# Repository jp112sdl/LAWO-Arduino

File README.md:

# LAWO-FlipDot
Arduino library for LAWO XY5 flipdot displays (also for GORBA and other FP2800 based flipdot displays)

### BOM (mostly from reichelt.de)

| Qty	| Reference(s)	| Value |	Order No. / URL	| Supplier
|------|------------|---------------|-------------|-------------|
|1|	C1	|100u	|RAD 100/25|	reichelt
|3 |	C2, C3, C4|100n|	X7R-5 100N	|reichelt
|1|	F1	|T500mA	|RND 170-00041	|reichelt
|1|	F1	|Fuse Holder |RND 170-00188 |reichelt
|1|P1	|MATRIX	|WSL 50G	|reichelt
|1|P2	|MUX|	WSL 20G	|reichelt
|1|Q1	|BC547|	BC 547C	|reichelt
|1|Q2	|IRF740	|IRF 740	|reichelt
|1|	R4|	56|	2W METALL 56	|reichelt
|1|	RV1|	5k|	64W-5,0K|	reichelt
|1	|U1|LC78_05-0.5	|LC78_05-0.5	|reichelt
|1|	U2	|LM317T	|LM 317-220	|reichelt
|1| J1 | Barrel Jack | DC BU25 90|reichelt
|1| J2 | 1x6 Screw Terminal Block, 5mm | RND 205-00049 |reichelt
|1| D1| 1N4001 | 1N 4001|reichelt|
|1| D2| LED1 | LED 3MM GN |reichelt|
|1| D3| LED2 | LED 3MM RT|reichelt
|2| SW1, SW2| TASTER 9303 | reichelt
|4| U4,U5,U6,U7	|Sockel	|GS 18	|reichelt
|2|U8,U9	|Sockel	|GS 28-S	|reichelt
|2| U5,U4	|ULN2803A	|ULN 2803A|	reichelt
|2	|U6,U7	|UDN2981A	|UDN 2981	|reichelt
|2| U8, U9 | MCP23017 | MCP 23017-E/SP | reichelt
|2| R13, R14 | 330 SMD 0805 | RND 0805 1 330 | reichelt
|1| R3 | 240 SMD 0805 | RND 0805 1 240 | reichelt
|2| R17, R18 | 4k7 SMD 0805 | RND 0805 1 4,7K  | reichelt
|12| R1, R2, R5, R6, R7, R8, R9, R10, R11, R12, R15, R16 | 10k SMD 0805 | RND 0805 1 10K  | reichelt
| 1 | U3 | ESP32 Module | AZDelivery ESP32 NodeMCU Module | [amazon.de](https://www.amazon.de/AZDelivery-NodeMCU-Development-Nachfolgermodell-ESP8266/dp/B071P98VTG/ref=sxts_sxwds-bia-wc-p13n1_0)

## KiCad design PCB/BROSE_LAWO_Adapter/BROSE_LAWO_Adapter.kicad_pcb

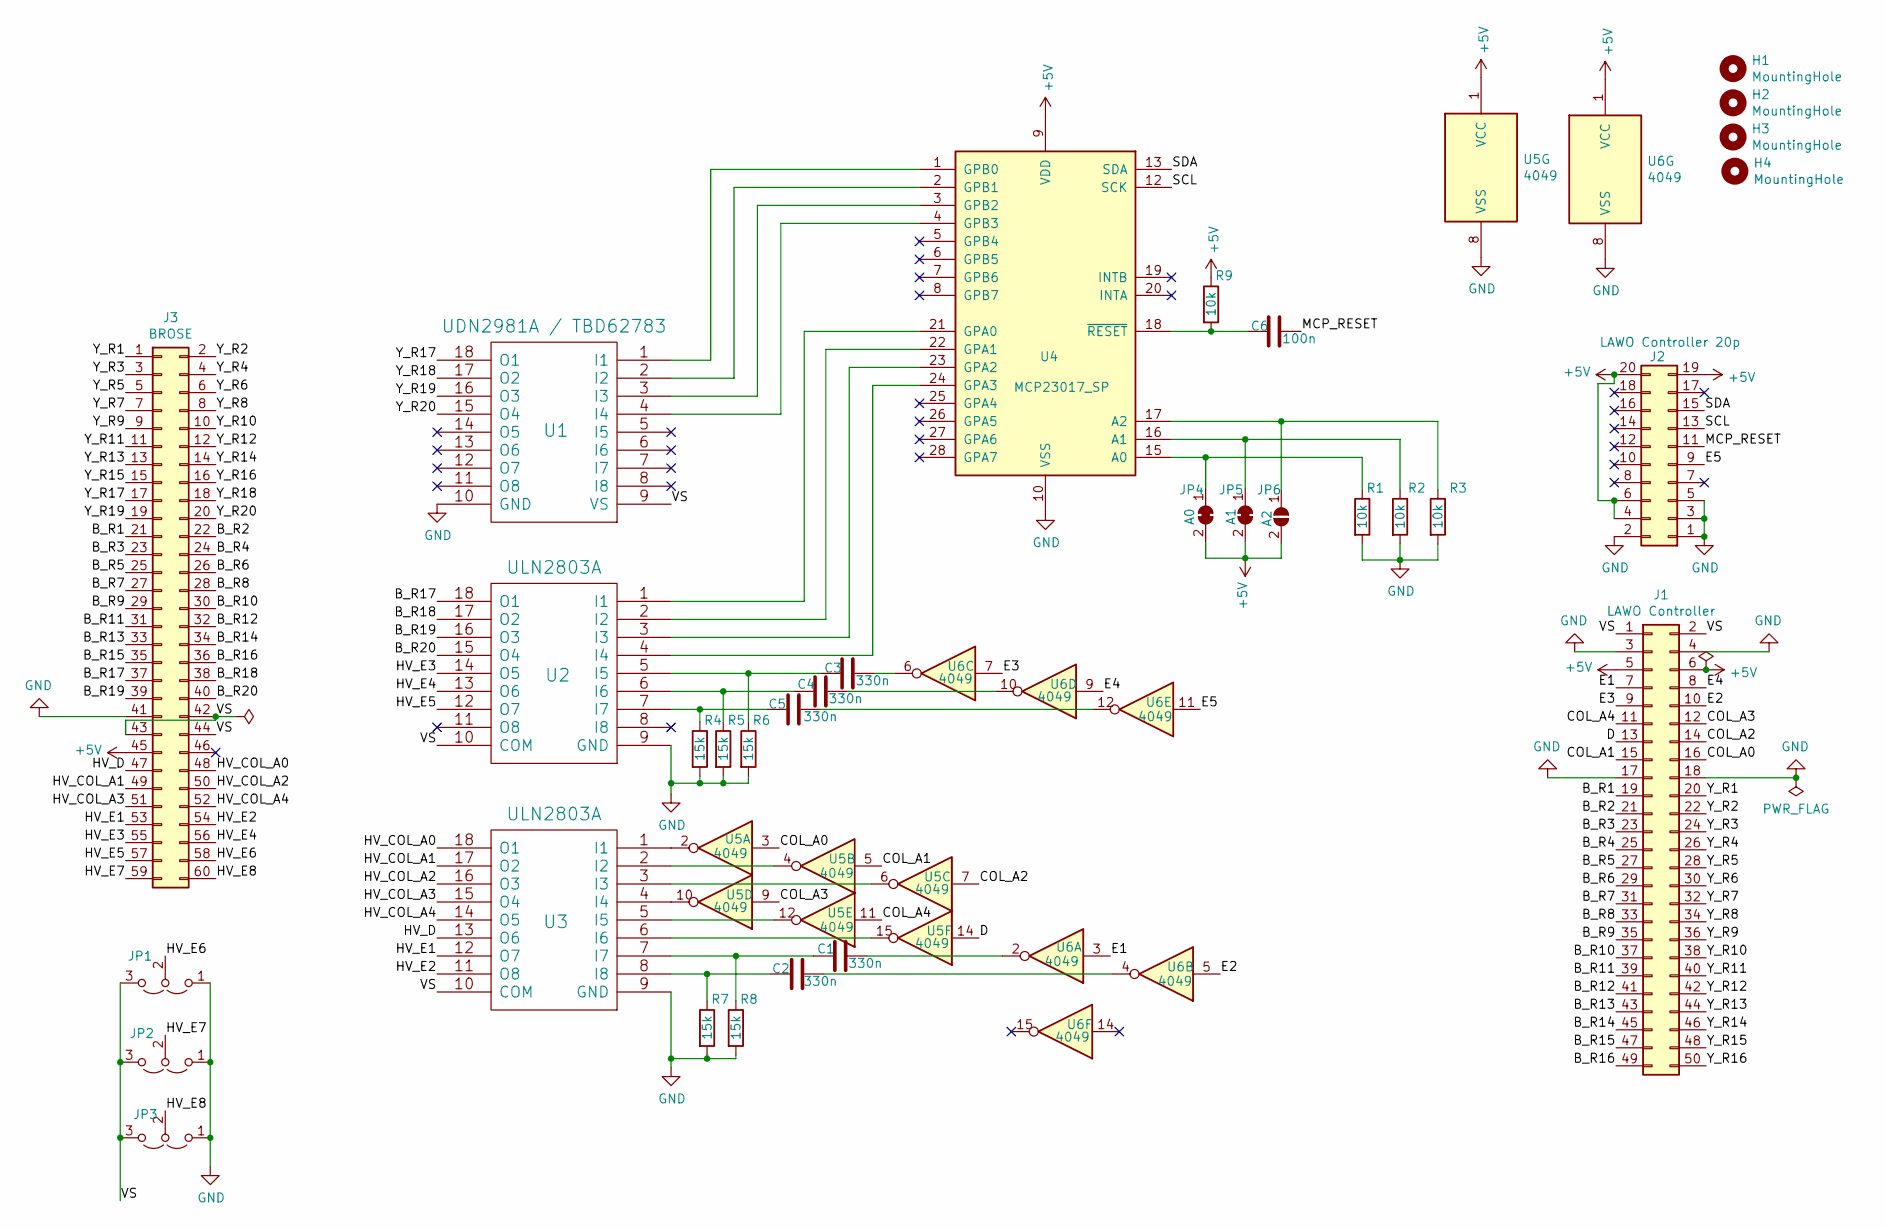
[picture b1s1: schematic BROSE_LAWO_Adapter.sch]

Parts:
C1, C2, C3, C4, C5: 330n; C_Rect_L10.0mm_W4.0mm_P7.50mm_MKS4
C6: 100n; C_0805_2012Metric_Pad1.15x1.40mm_HandSolder
H1, H2, H3, H4: MountingHole; 1pin
J1: LAWO Controller; IDC-Header_2x25_P2.54mm_Vertical
J2: LAWO Controller 20p; IDC-Header_2x10_P2.54mm_Vertical
J3: BROSE; IDC-Header_2x30_P2.54mm_Vertical
JP1: E6; PinHeader_1x03_P2.54mm_Vertical
JP2: E7; PinHeader_1x03_P2.54mm_Vertical
JP3: E8; PinHeader_1x03_P2.54mm_Vertical
JP4: A0; SolderJumper-2_P1.3mm_Bridged_RoundedPad1.0x1.5mm
JP5: A1; SolderJumper-2_P1.3mm_Bridged_RoundedPad1.0x1.5mm
JP6: A2; SolderJumper-2_P1.3mm_Open_RoundedPad1.0x1.5mm
R1, R2, R3, R9: 10k; R_0805_2012Metric_Pad1.15x1.40mm_HandSolder
R4, R5, R6, R7, R8: 15k; R_Axial_DIN0204_L3.6mm_D1.6mm_P2.54mm_Vertical
U1: UDN2981A / TBD62783; DIP-18_W7.62mm_Socket
U2, U3: ULN2803A; DIP-18_W7.62mm_Socket
U4: MCP23017_SP; DIP-28_W7.62mm_Socket
U5, U6: 4049; DIP-16_W7.62mm_Socket

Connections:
+5V: J1.5, J1.6, J2.4, J2.6, J2.19, J2.20, J3.45, JP4.2 (B), JP5.2 (B), JP6.2 (B), R9.1, U4.9 (VDD), U5.1 (VCC), U6.1 (VCC)
/B_R1: J1.19, J3.21
/B_R2: J1.21, J3.22
/B_R3: J1.23, J3.23
/B_R4: J1.25, J3.24
/B_R5: J1.27, J3.25
/B_R6: J1.29, J3.26
/B_R7: J1.31, J3.27
/B_R8: J1.33, J3.28
/B_R9: J1.35, J3.29
/B_R10: J1.37, J3.30
/B_R11: J1.39, J3.31
/B_R12: J1.41, J3.32
/B_R13: J1.43, J3.33
/B_R14: J1.45, J3.34
/B_R15: J1.47, J3.35
/B_R16: J1.49, J3.36
/B_R17: J3.37, U2.18 (O1)
/B_R18: J3.38, U2.17 (O2)
/B_R19: J3.39, U2.16 (O3)
/B_R20: J3.40, U2.15 (O4)
/COL_A0: J1.16, U5.3
/COL_A1: J1.15, U5.5
/COL_A2: J1.14, U5.7
/COL_A3: J1.12, U5.9
/COL_A4: J1.11, U5.11
/D: J1.13, U5.14
/E1: J1.7, U6.3
/E2: J1.10, U6.5
/E3: J1.9, U6.7
/E4: J1.8, U6.9
/E5: J2.9, U6.11
/HV_COL_A0: J3.48, U3.18 (O1)
/HV_COL_A1: J3.49, U3.17 (O2)
/HV_COL_A2: J3.50, U3.16 (O3)
/HV_COL_A3: J3.51, U3.15 (O4)
/HV_COL_A4: J3.52, U3.14 (O5)
/HV_D: J3.47, U3.13 (O6)
/HV_E1: J3.53, U3.12 (O7)
/HV_E2: J3.54, U3.11 (O8)
/HV_E3: J3.55, U2.14 (O5)
/HV_E4: J3.56, U2.13 (O6)
/HV_E5: J3.57, U2.12 (O7)
/HV_E6: J3.58, JP1.2 (C)
/HV_E7: J3.59, JP2.2 (C)
/HV_E8: J3.60, JP3.2 (C)
/MCP_RESET: C6.2, J2.11
/SCL: J2.13, U4.12 (SCK)
/SDA: J2.15, U4.13 (SDA)
/VS: J1.1, J1.2, J3.42, J3.43, J3.44, JP1.3 (B), JP2.3 (B), JP3.3 (B), U1.9 (VS), U2.10 (COM), U3.10 (COM)
/Y_R1: J1.20, J3.1
/Y_R2: J1.22, J3.2
/Y_R3: J1.24, J3.3
/Y_R4: J1.26, J3.4
/Y_R5: J1.28, J3.5
/Y_R6: J1.30, J3.6
/Y_R7: J1.32, J3.7
/Y_R8: J1.34, J3.8
/Y_R9: J1.36, J3.9
/Y_R10: J1.38, J3.10
/Y_R11: J1.40, J3.11
/Y_R12: J1.42, J3.12
/Y_R13: J1.44, J3.13
/Y_R14: J1.46, J3.14
/Y_R15: J1.48, J3.15
/Y_R16: J1.50, J3.16
/Y_R17: J3.17, U1.18 (O1)
/Y_R18: J3.18, U1.17 (O2)
/Y_R19: J3.19, U1.16 (O3)
/Y_R20: J3.20, U1.15 (O4)
GND: J1.3, J1.4, J1.17, J1.18, J2.1, J2.2, J2.3, J2.5, J3.41, JP1.1 (A), JP2.1 (A), JP3.1 (A), R1.2, R2.2, R3.2, R4.2, R5.2, R6.2, R7.2, R8.2, U1.10 (GND), U2.9 (GND), U3.9 (GND), U4.10 (VSS), U5.8 (VSS), U6.8 (VSS)
unnamed: C1.1, R8.1, U3.7 (I7)
unnamed: C1.2, U6.2
unnamed: C2.1, R7.1, U3.8 (I8)
unnamed: C2.2, U6.4
unnamed: C3.1, R6.1, U2.5 (I5)
unnamed: C3.2, U6.6
unnamed: C4.1, R5.1, U2.6 (I6)
unnamed: C4.2, U6.10
unnamed: C5.1, R4.1, U2.7 (I7)
unnamed: C5.2, U6.12
unnamed: C6.1, R9.2, U4.18 (~RESET~)
unnamed: JP4.1 (A), R1.1, U4.15 (A0)
unnamed: JP5.1 (A), R2.1, U4.16 (A1)
unnamed: JP6.1 (A), R3.1, U4.17 (A2)
unnamed: U1.1 (I1), U4.1 (GPB0)
unnamed: U1.2 (I2), U4.2 (GPB1)
unnamed: U1.3 (I3), U4.3 (GPB2)
unnamed: U1.4 (I4), U4.4 (GPB3)
unnamed: U2.1 (I1), U4.21 (GPA0)
unnamed: U2.2 (I2), U4.22 (GPA1)
unnamed: U2.3 (I3), U4.23 (GPA2)
unnamed: U2.4 (I4), U4.24 (GPA3)
unnamed: U3.1 (I1), U5.2
unnamed: U3.2 (I2), U5.4
unnamed: U3.3 (I3), U5.6
unnamed: U3.4 (I4), U5.10
unnamed: U3.5 (I5), U5.12
unnamed: U3.6 (I6), U5.15

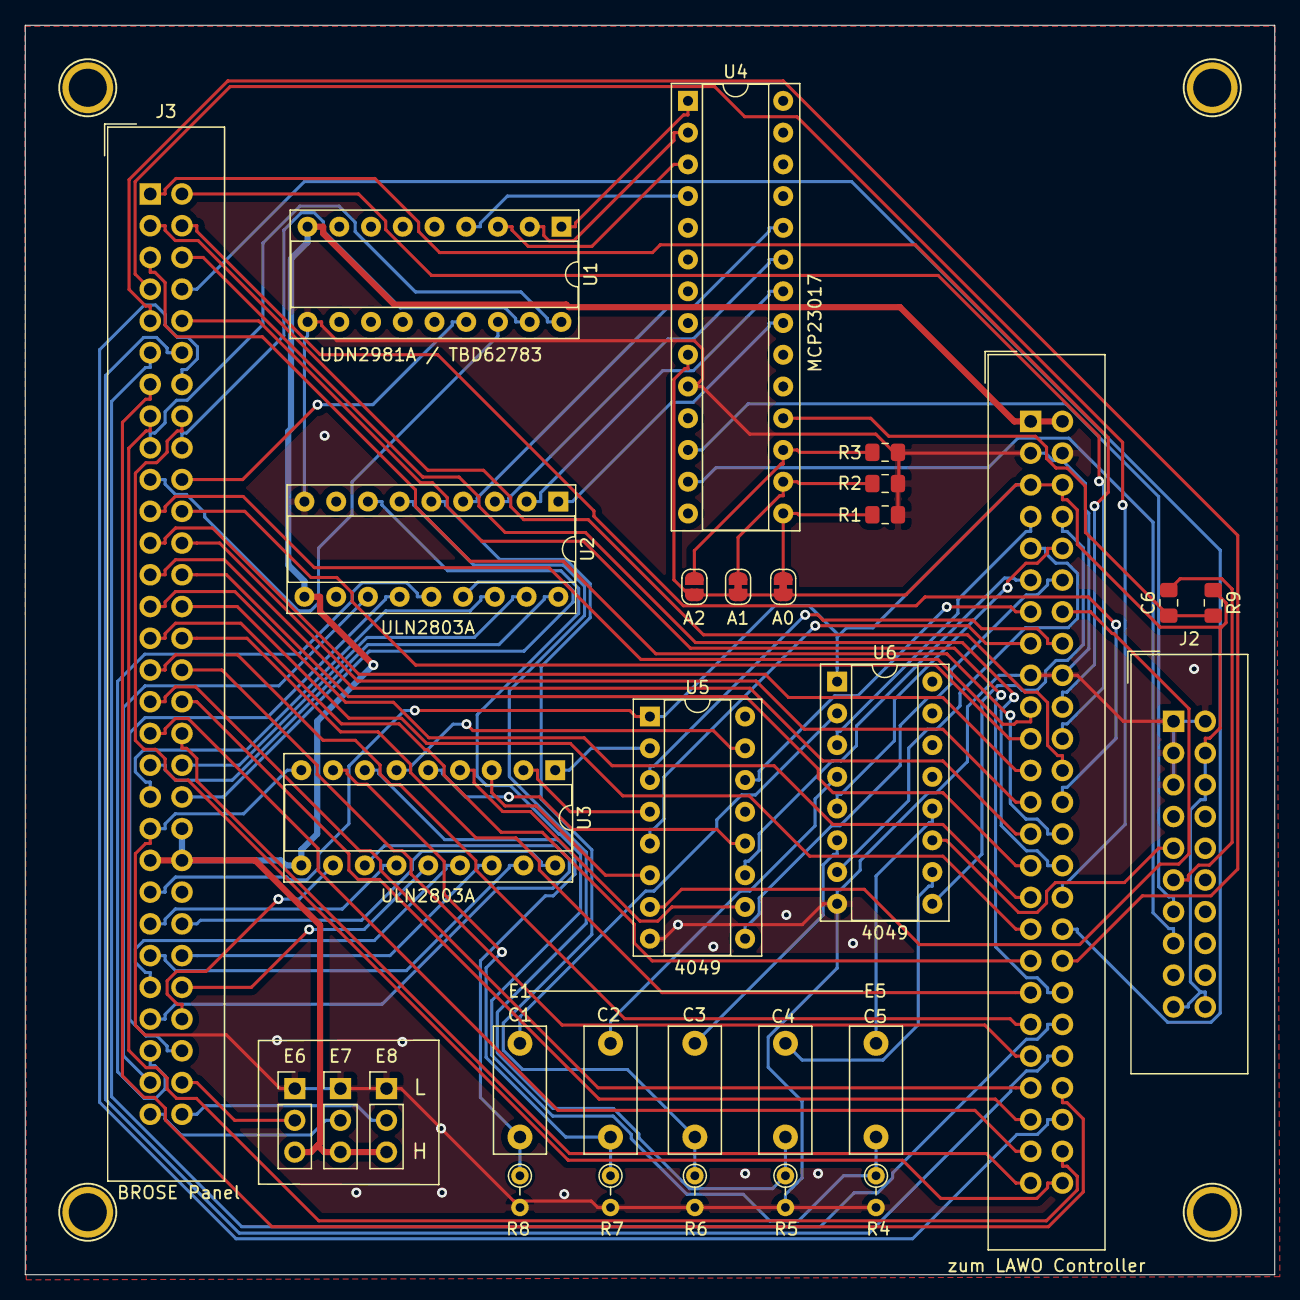
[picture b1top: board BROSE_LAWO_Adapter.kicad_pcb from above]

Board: 2 copper layers, 100.0 x 100.0 mm, 34 parts (0 on the bottom side), 99 nets.

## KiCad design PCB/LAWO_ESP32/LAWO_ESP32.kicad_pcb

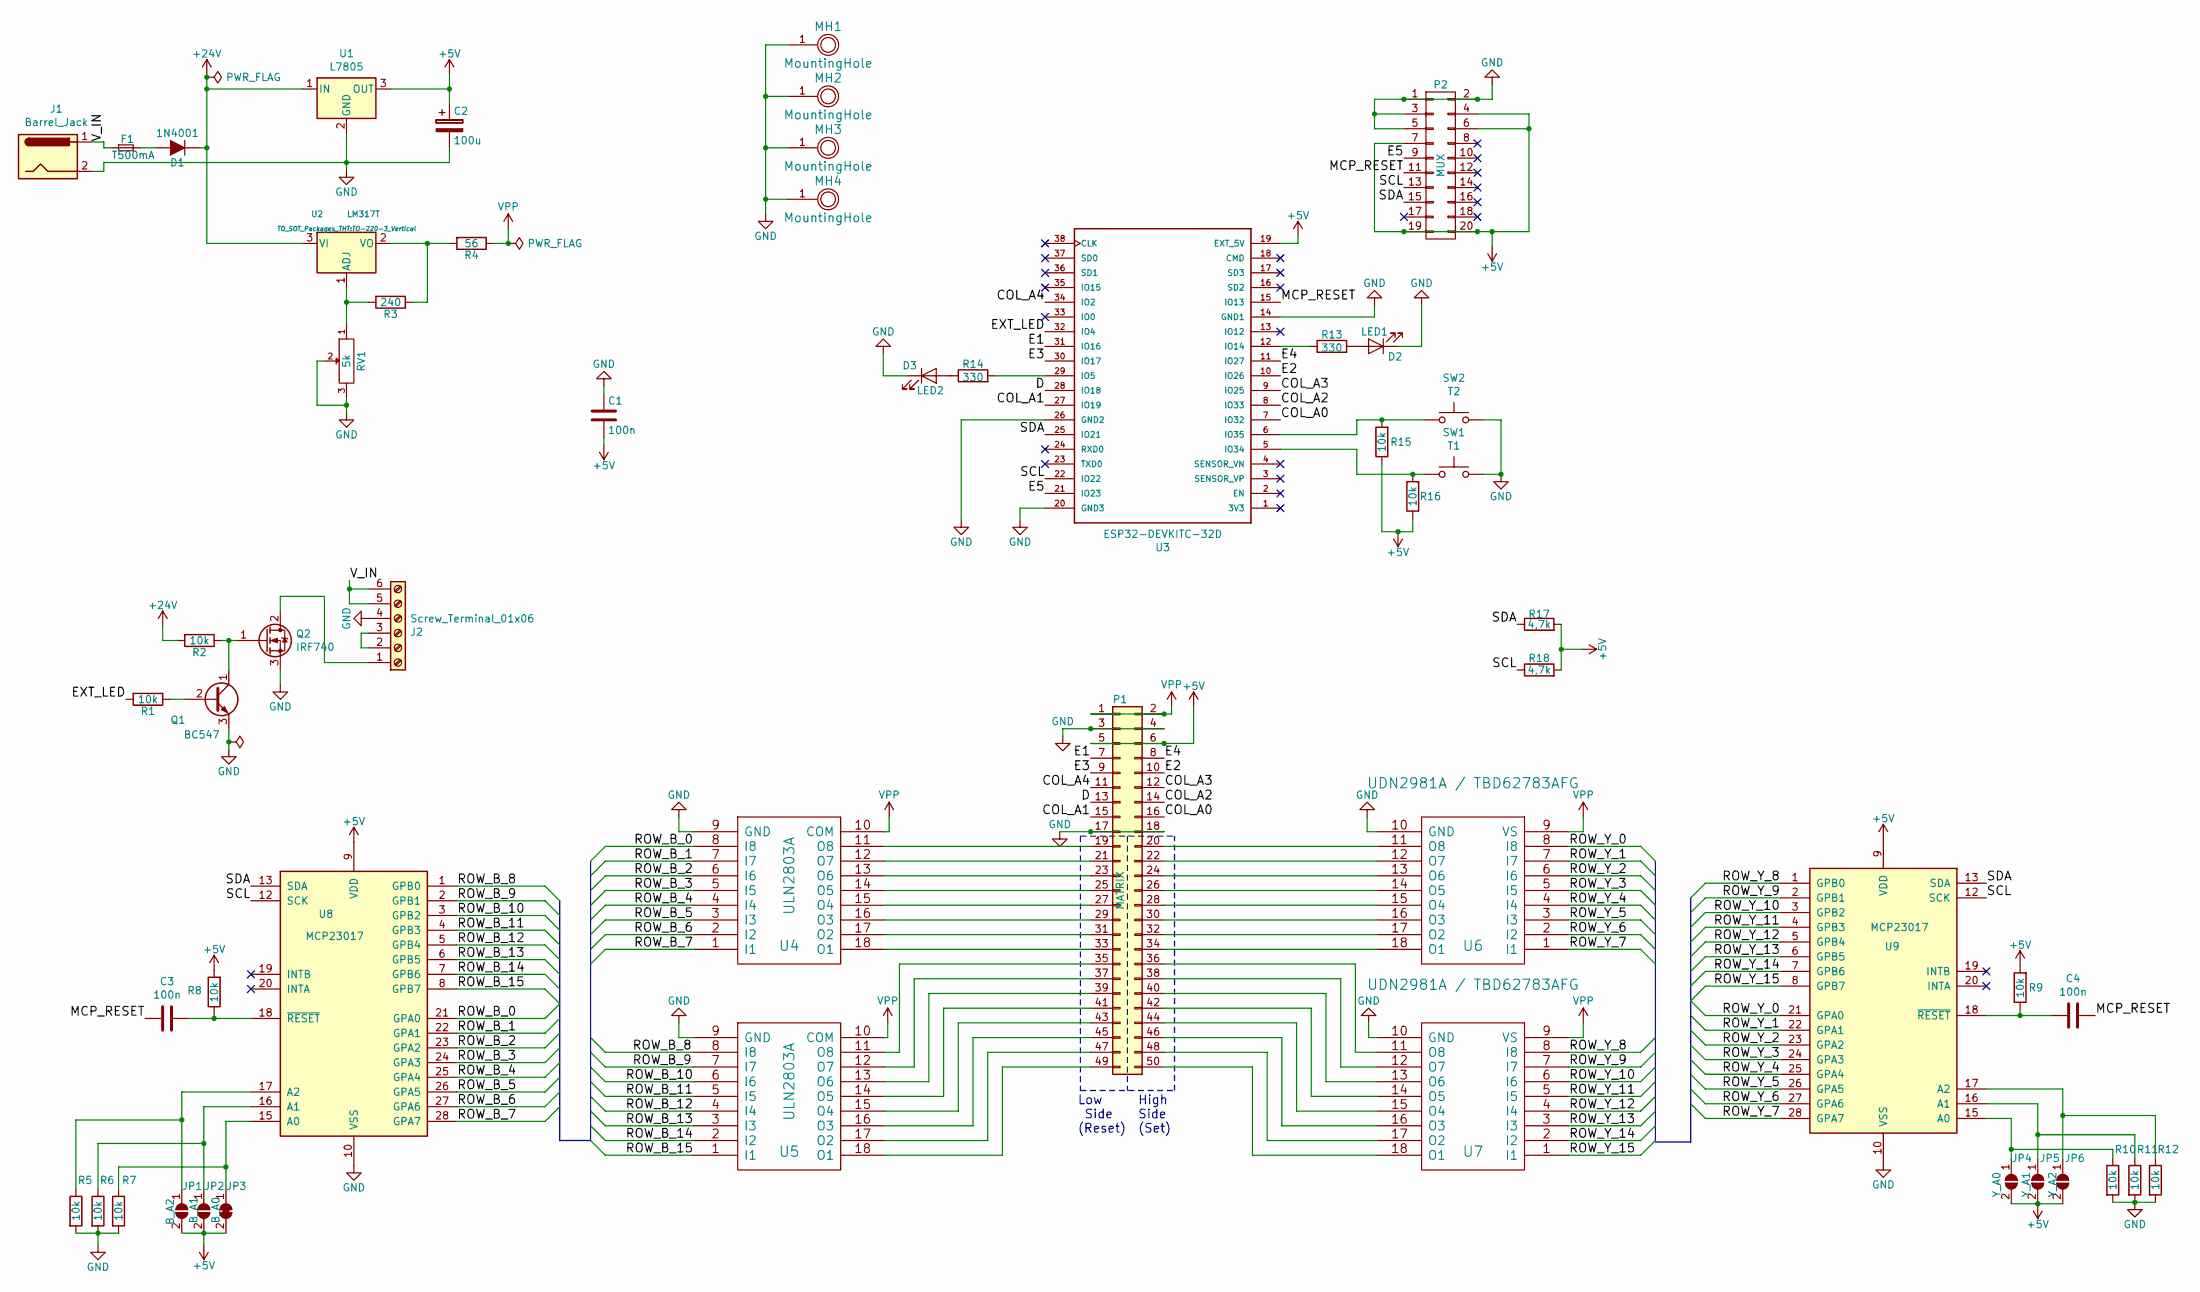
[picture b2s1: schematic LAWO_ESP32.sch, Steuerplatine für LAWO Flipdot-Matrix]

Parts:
C1, C3, C4: 100n; C_0805_2012Metric_Pad1.15x1.40mm_HandSolder
C2: 100u; CP_Radial_D5.0mm_P2.00mm
D1: 1N4001; D_DO-41_SOD81_P10.16mm_Horizontal
D2: LED1; LED_D3.0mm
D3: LED2; LED_D3.0mm
F1: T500mA; Fuseholder5x20_horiz_open_Schurter_0031_8201
J1: Barrel_Jack; BARREL_JACK
J2: Screw_Terminal_01x06; TerminalBlock_bornier-6_P5.08mm
JP1: B_A2; SolderJumper-2_P1.3mm_Open_RoundedPad1.0x1.5mm
JP2: B_A1; SolderJumper-2_P1.3mm_Open_RoundedPad1.0x1.5mm
JP3: B_A0; SolderJumper-2_P1.3mm_Bridged2Bar_RoundedPad1.0x1.5mm
JP4: Y_A0; SolderJumper-2_P1.3mm_Open_RoundedPad1.0x1.5mm
JP5: Y_A1; SolderJumper-2_P1.3mm_Open_RoundedPad1.0x1.5mm
JP6: Y_A2; SolderJumper-2_P1.3mm_Open_RoundedPad1.0x1.5mm
MH1, MH2, MH3, MH4: MountingHole; 1pin
P1: MATRIX; IDC_Header_Straight_50pins
P2: MUX; IDC_Header_Straight_20pins
Q1: BC547; TO-92_HandSolder
Q2: IRF740; TO-220-3_Vertical
R1, R2, R5, R6, R7, R8, R9, R10, R11, R12, R15, R16: 10k; R_0805_2012Metric
R3: 240; R_0805_2012Metric
R4: 56; R_Axial_DIN0411_L9.9mm_D3.6mm_P15.24mm_Horizontal
R13, R14: 330; R_0805_2012Metric
R17, R18: 4,7k; R_0805_2012Metric
RV1: 5k; Potentiometer_Trimmer_Bourns_3299W
SW1: T1; SW_PUSH_6mm_h5mm
SW2: T2; SW_PUSH_6mm_h5mm
U1: L7805; SIP3_11.6x8.5mm
U2: LM317T; TO-220-3_Vertical
U3: ESP32-DEVKITC-32D; MODULE_ESP32-DEVKITC-32D
U4, U5: ULN2803A; DIP-18_W7.62mm_Socket
U6, U7: UDN2981A / TBD62783AFG; DIP-18_W7.62mm_Socket
U8, U9: MCP23017; DIP-28_W7.62mm_Socket

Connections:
+5V: C1.2, C2.1, JP1.2 (B), JP2.2 (B), JP3.2 (B), JP4.2 (B), JP5.2 (B), JP6.2 (B), P1.5, P1.6, P2.4, P2.6, P2.7, P2.19, P2.20, R8.2, R9.2, R15.1, R16.1, R17.2, R18.2, U1.3 (OUT), U3.19 (EXT_5V), U8.9 (VDD), U9.9 (VDD)
+24V: D1.1 (K), R2.2, U1.1 (IN), U2.3 (VI)
/COL_A0: P1.16, U3.7 (IO32)
/COL_A1: P1.15, U3.27 (IO19)
/COL_A2: P1.14, U3.8 (IO33)
/COL_A3: P1.12, U3.9 (IO25)
/COL_A4: P1.11, U3.34 (IO2)
/D: P1.13, U3.28 (IO18)
/E1: P1.7, U3.31 (IO16)
/E2: P1.10, U3.10 (IO26)
/E3: P1.9, U3.30 (IO17)
/E4: P1.8, U3.11 (IO27)
/E5: P2.9, U3.21 (IO23)
/EXT_LED: R1.2, U3.32 (IO4)
/MCP_RESET: C3.2, C4.1, P2.11, U3.15 (IO13)
/ROW_B_0: U4.8 (I8), U8.21 (GPA0)
/ROW_B_1: U4.7 (I7), U8.22 (GPA1)
/ROW_B_2: U4.6 (I6), U8.23 (GPA2)
/ROW_B_3: U4.5 (I5), U8.24 (GPA3)
/ROW_B_4: U4.4 (I4), U8.25 (GPA4)
/ROW_B_5: U4.3 (I3), U8.26 (GPA5)
/ROW_B_6: U4.2 (I2), U8.27 (GPA6)
/ROW_B_7: U4.1 (I1), U8.28 (GPA7)
/ROW_B_8: U5.8 (I8), U8.1 (GPB0)
/ROW_B_9: U5.7 (I7), U8.2 (GPB1)
/ROW_B_10: U5.6 (I6), U8.3 (GPB2)
/ROW_B_11: U5.5 (I5), U8.4 (GPB3)
/ROW_B_12: U5.4 (I4), U8.5 (GPB4)
/ROW_B_13: U5.3 (I3), U8.6 (GPB5)
/ROW_B_14: U5.2 (I2), U8.7 (GPB6)
/ROW_B_15: U5.1 (I1), U8.8 (GPB7)
/ROW_Y_0: U6.8 (I8), U9.21 (GPA0)
/ROW_Y_1: U6.7 (I7), U9.22 (GPA1)
/ROW_Y_2: U6.6 (I6), U9.23 (GPA2)
/ROW_Y_3: U6.5 (I5), U9.24 (GPA3)
/ROW_Y_4: U6.4 (I4), U9.25 (GPA4)
/ROW_Y_5: U6.3 (I3), U9.26 (GPA5)
/ROW_Y_6: U6.2 (I2), U9.27 (GPA6)
/ROW_Y_7: U6.1 (I1), U9.28 (GPA7)
/ROW_Y_8: U7.8 (I8), U9.1 (GPB0)
/ROW_Y_9: U7.7 (I7), U9.2 (GPB1)
/ROW_Y_10: U7.6 (I6), U9.3 (GPB2)
/ROW_Y_11: U7.5 (I5), U9.4 (GPB3)
/ROW_Y_12: U7.4 (I4), U9.5 (GPB4)
/ROW_Y_13: U7.3 (I3), U9.6 (GPB5)
/ROW_Y_14: U7.2 (I2), U9.7 (GPB6)
/ROW_Y_15: U7.1 (I1), U9.8 (GPB7)
/SCL: P2.13, R18.1, U3.22 (IO22), U8.12 (SCK), U9.12 (SCK)
/SDA: P2.15, R17.1, U3.25 (IO21), U8.13 (SDA), U9.13 (SDA)
/V_IN: F1.1, J1.1, J2.5, J2.6
GND: C1.1, C2.2, D2.1 (K), D3.1 (K), J1.2, J2.4, MH1.1, MH2.1, MH3.1, MH4.1, P1.3, P1.4, P1.17, P1.18, P2.1, P2.2, P2.3, P2.5, Q1.3 (E), Q2.3 (S), R5.2, R6.2, R7.2, R10.2, R11.2, R12.2, RV1.2, RV1.3, SW1.2, SW2.2, U1.2 (GND), U3.14 (GND1), U3.20 (GND3), U3.26 (GND2), U4.9 (GND), U5.9 (GND), U6.10 (GND), U7.10 (GND), U8.10 (VSS), U9.10 (VSS)
unnamed: C3.1, R8.1, U8.18 (~RESET~)
unnamed: C4.2, R9.1, U9.18 (~RESET~)
unnamed: D1.2 (A), F1.2
unnamed: D2.2 (A), R13.2
unnamed: D3.2 (A), R14.1
unnamed: J2.1, Q2.2 (D)
unnamed: J2.2, J2.3
unnamed: JP1.1 (A), R5.1, U8.17 (A2)
unnamed: JP2.1 (A), R6.1, U8.16 (A1)
unnamed: JP3.1 (A), R7.1, U8.15 (A0)
unnamed: JP4.1 (A), R10.1, U9.15 (A0)
unnamed: JP5.1 (A), R11.1, U9.16 (A1)
unnamed: JP6.1 (A), R12.1, U9.17 (A2)
unnamed: P1.19, U4.11 (O8)
unnamed: P1.20, U6.11 (O8)
unnamed: P1.21, U4.12 (O7)
unnamed: P1.22, U6.12 (O7)
unnamed: P1.23, U4.13 (O6)
unnamed: P1.24, U6.13 (O6)
unnamed: P1.25, U4.14 (O5)
unnamed: P1.26, U6.14 (O5)
unnamed: P1.27, U4.15 (O4)
unnamed: P1.28, U6.15 (O4)
unnamed: P1.29, U4.16 (O3)
unnamed: P1.30, U6.16 (O3)
unnamed: P1.31, U4.17 (O2)
unnamed: P1.32, U6.17 (O2)
unnamed: P1.33, U4.18 (O1)
unnamed: P1.34, U6.18 (O1)
unnamed: P1.35, U5.11 (O8)
unnamed: P1.36, U7.11 (O8)
unnamed: P1.37, U5.12 (O7)
unnamed: P1.38, U7.12 (O7)
unnamed: P1.39, U5.13 (O6)
unnamed: P1.40, U7.13 (O6)
unnamed: P1.41, U5.14 (O5)
unnamed: P1.42, U7.14 (O5)
unnamed: P1.43, U5.15 (O4)
unnamed: P1.44, U7.15 (O4)
unnamed: P1.45, U5.16 (O3)
unnamed: P1.46, U7.16 (O3)
unnamed: P1.47, U5.17 (O2)
unnamed: P1.48, U7.17 (O2)
unnamed: P1.49, U5.18 (O1)
unnamed: P1.50, U7.18 (O1)
unnamed: Q1.1 (C), Q2.1 (G), R2.1
unnamed: Q1.2 (B), R1.1
unnamed: R3.1, R4.2, U2.2 (VO)
unnamed: R3.2, RV1.1, U2.1 (ADJ)
unnamed: R13.1, U3.12 (IO14)
unnamed: R14.2, U3.29 (IO5)
unnamed: R15.2, SW2.1, U3.6 (IO35)
unnamed: R16.2, SW1.1, U3.5 (IO34)
VPP: P1.1, P1.2, R4.1, U4.10 (COM), U5.10 (COM), U6.9 (VS), U7.9 (VS)

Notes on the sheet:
Low Side (Reset)
High Side (Set)

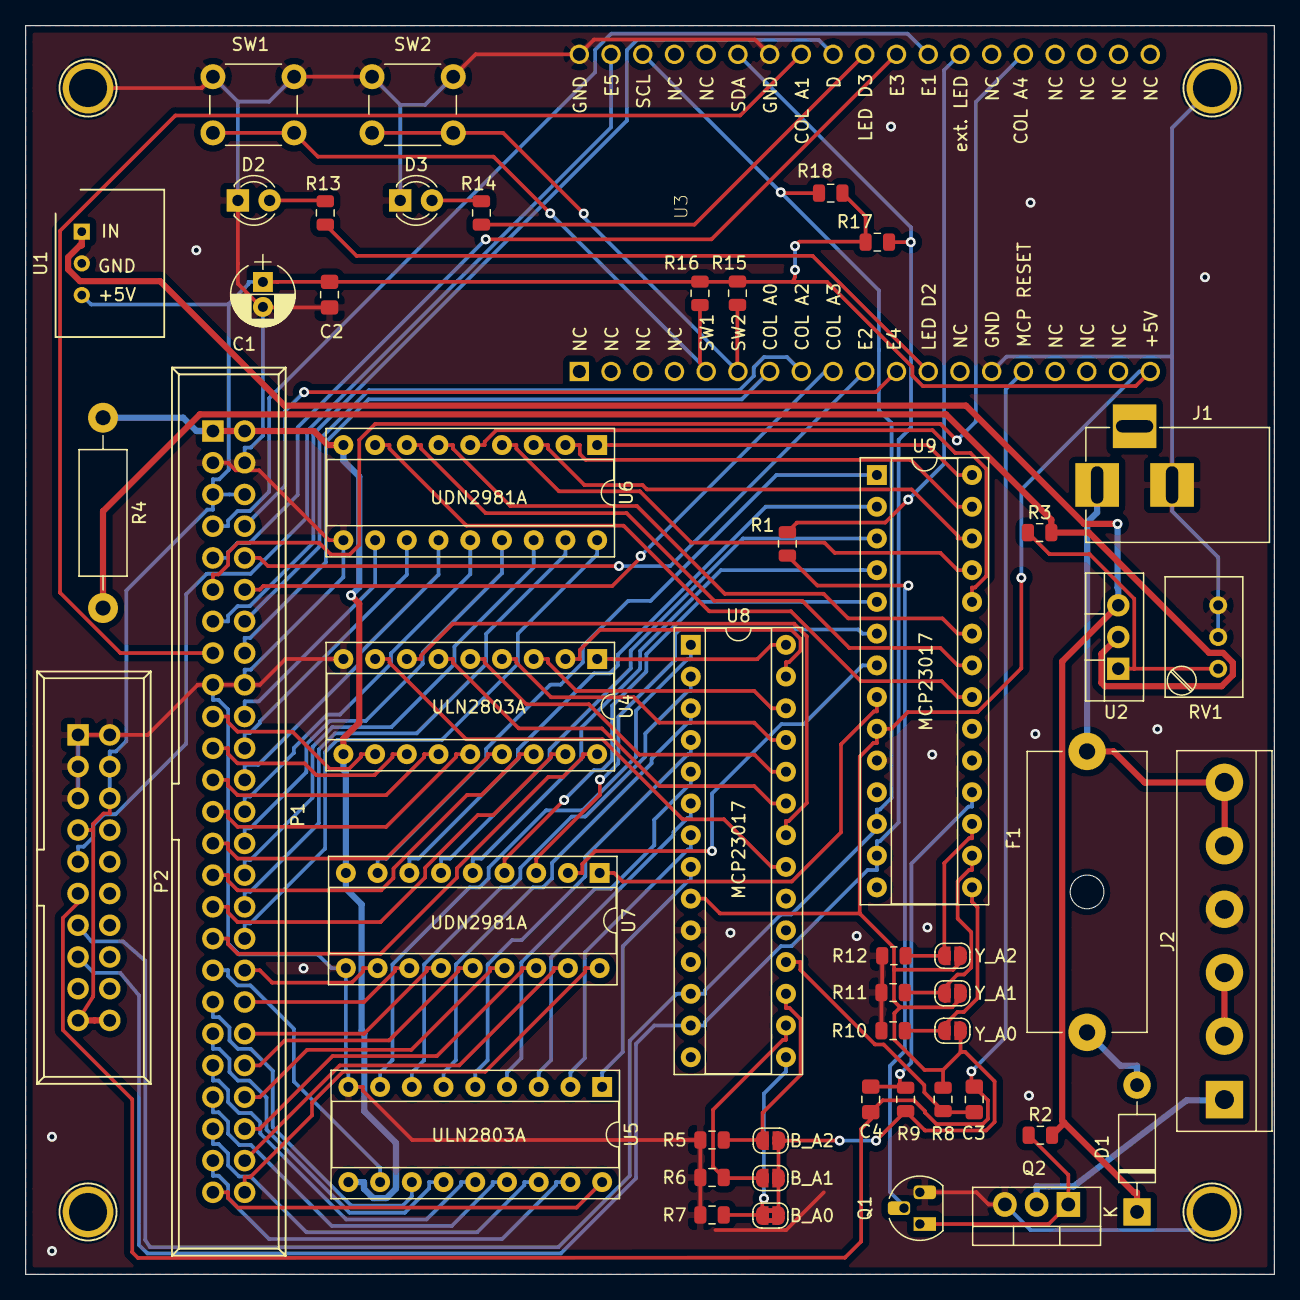
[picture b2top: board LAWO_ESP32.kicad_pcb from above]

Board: 2 copper layers, 100.0 x 100.0 mm, 54 parts (0 on the bottom side), 105 nets.

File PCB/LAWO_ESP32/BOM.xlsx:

Reference | Value | Footprint | Datasheet | Feld4
C1 | 100n | Capacitor_SMD:C_0805_2012Metric_Pad1.15x1.40mm_HandSolder
C2 | 100u | Capacitors_THT:CP_Radial_D5.0mm_P2.00mm
C3 | 100n | Capacitor_SMD:C_0805_2012Metric_Pad1.15x1.40mm_HandSolder | ~
C4 | 100n | Capacitor_SMD:C_0805_2012Metric_Pad1.15x1.40mm_HandSolder | ~
D1 | 1N4001 | Diode_THT:D_DO-41_SOD81_P10.16mm_Horizontal
D2 | LED1 | LED_THT:LED_D3.0mm | ~
D3 | LED2 | LED_THT:LED_D3.0mm | ~
F1 | T500mA | Fuse_Holders_and_Fuses:Fuseholder5x20_horiz_open_Schurter_0031_8201
J1 | Barrel_Jack | Connectors:BARREL_JACK | ~
J2 | Screw_Terminal_01x06 | Connectors_Terminal_Blocks:TerminalBlock_bornier-6_P5.08mm | ~
P1 | MATRIX | Connect:IDC_Header_Straight_50pins
P2 | MUX | Connect:IDC_Header_Straight_20pins
Q1 | BC547 | Package_TO_SOT_THT:TO-92_HandSolder | http://www.fairchildsemi.com/ds/BC/BC547.pdf
Q2 | IRF740 | Package_TO_SOT_THT:TO-220-3_Vertical | http://www.vishay.com/docs/91054/91054.pdf
R1 | 10k | Resistor_SMD:R_0805_2012Metric
R10 | 10k | Resistor_SMD:R_0805_2012Metric | ~
R11 | 10k | Resistor_SMD:R_0805_2012Metric | ~
R12 | 10k | Resistor_SMD:R_0805_2012Metric | ~
R13 | 330 | Resistor_SMD:R_0805_2012Metric | ~
R14 | 330 | Resistor_SMD:R_0805_2012Metric | ~
R15 | 10k | Resistor_SMD:R_0805_2012Metric
R16 | 10k | Resistor_SMD:R_0805_2012Metric
R17 | 4,7k | Resistor_SMD:R_0805_2012Metric | ~
R18 | 4,7k | Resistor_SMD:R_0805_2012Metric | ~
R2 | 10k | Resistor_SMD:R_0805_2012Metric
R3 | 240 | Resistor_SMD:R_0805_2012Metric
R4 | 56 | Resistor_THT:R_Axial_DIN0411_L9.9mm_D3.6mm_P15.24mm_Horizontal
R5 | 10k | Resistor_SMD:R_0805_2012Metric | ~
R6 | 10k | Resistor_SMD:R_0805_2012Metric | ~
R7 | 10k | Resistor_SMD:R_0805_2012Metric | ~
R8 | 10k | Resistor_SMD:R_0805_2012Metric | ~
R9 | 10k | Resistor_SMD:R_0805_2012Metric | ~
RV1 | 5k | Potentiometers:Potentiometer_Trimmer_Bourns_3299W
SW1 | T1 | Buttons_Switches_THT:SW_PUSH_6mm_h5mm | ~
SW2 | T2 | Buttons_Switches_THT:SW_PUSH_6mm_h5mm | ~
U1 | LC78_05-0.5 | Package_SIP:SIP3_11.6x8.5mm | http://www.st.com/content/ccc/resource/technical/document/da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
U2 | LM317T | TO_SOT_Packages_THT:TO-220-3_Vertical
U3 | ESP32-DEVKITC-32D | additional:MODULE_ESP32-DEVKITC-32D | Espressif Systems | 4
U4 | ULN2803A | Package_DIP:DIP-18_W7.62mm_Socket
U5 | ULN2803A | Package_DIP:DIP-18_W7.62mm_Socket
U6 | UDN2981A / TBD62783AFG | Package_DIP:DIP-18_W7.62mm_Socket
U7 | UDN2981A / TBD62783AFG | Package_DIP:DIP-18_W7.62mm_Socket
U8 | MCP23017 | Package_DIP:DIP-28_W7.62mm_Socket | http://ww1.microchip.com/downloads/en/DeviceDoc/20001952C.pdf
U9 | MCP23017 | Package_DIP:DIP-28_W7.62mm_Socket | http://ww1.microchip.com/downloads/en/DeviceDoc/20001952C.pdf

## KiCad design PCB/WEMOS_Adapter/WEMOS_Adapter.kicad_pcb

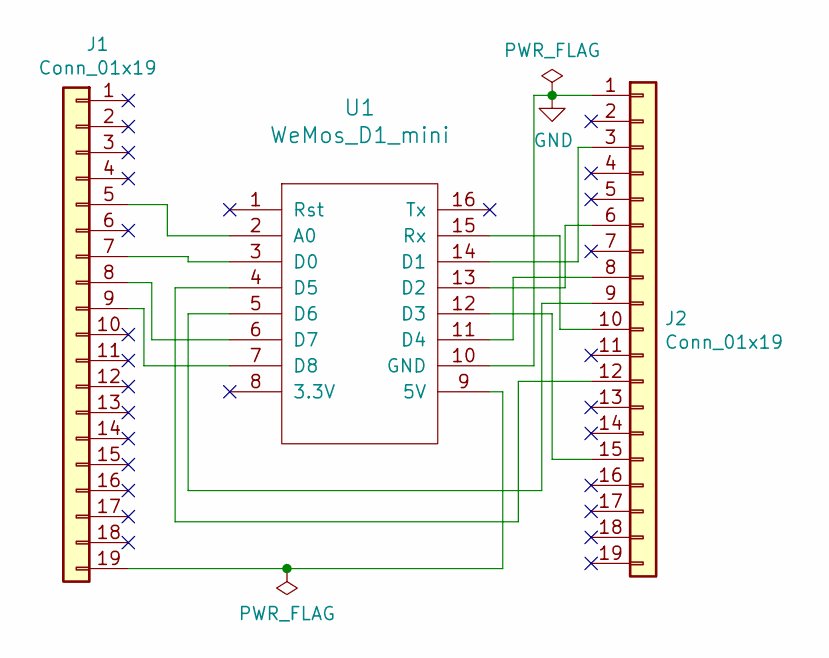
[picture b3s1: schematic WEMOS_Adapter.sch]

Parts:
J1, J2: Conn_01x19; PinHeader_1x19_P2.54mm_Vertical
U1: WeMos_D1_mini; wemos-d1-mini-connectors-only

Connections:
GND: J2.1, U1.10 (GND)
unnamed: J1.5, U1.2 (A0)
unnamed: J1.7, U1.3 (D0)
unnamed: J1.8, U1.6 (D7)
unnamed: J1.9, U1.7 (D8)
unnamed: J1.19, U1.9 (5V)
unnamed: J2.3, U1.14 (D1)
unnamed: J2.6, U1.13 (D2)
unnamed: J2.8, U1.11 (D4)
unnamed: J2.9, U1.5 (D6)
unnamed: J2.10, U1.15 (Rx)
unnamed: J2.12, U1.4 (D5)
unnamed: J2.15, U1.12 (D3)

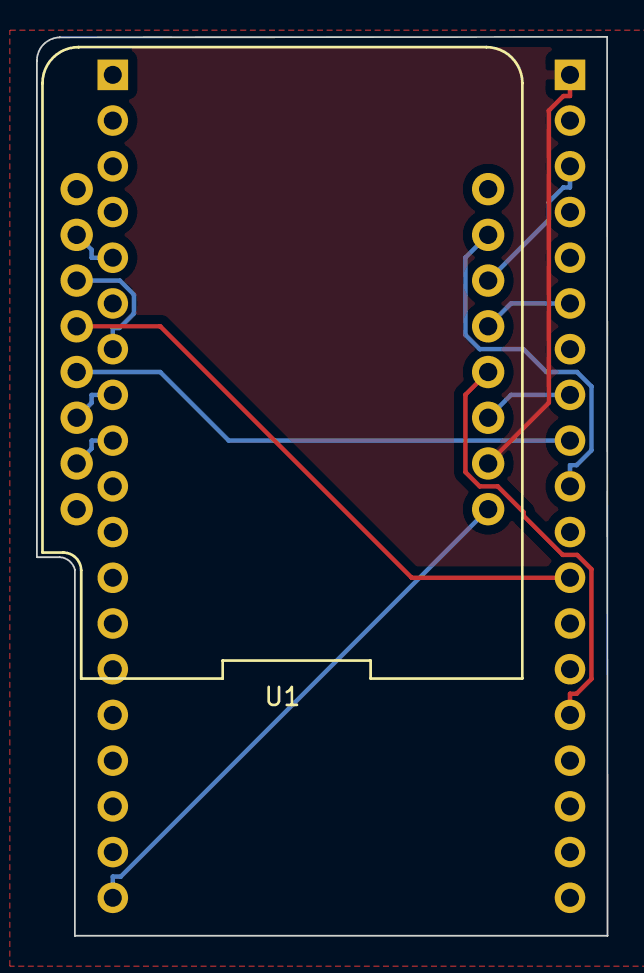
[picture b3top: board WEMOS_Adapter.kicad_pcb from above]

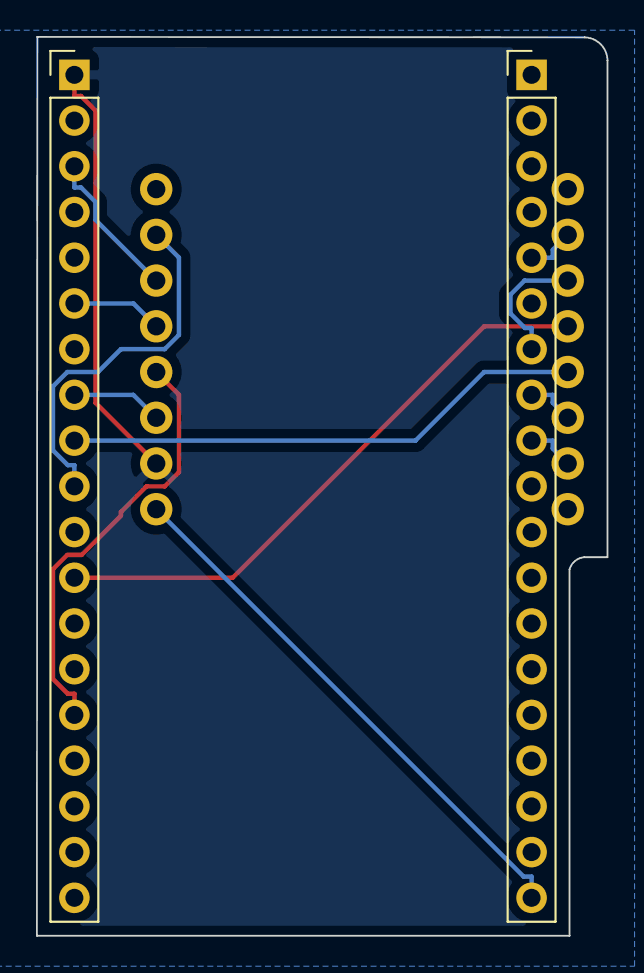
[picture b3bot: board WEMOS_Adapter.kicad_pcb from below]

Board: 2 copper layers, 31.7 x 49.9 mm, 3 parts (2 on the bottom side), 13 nets.

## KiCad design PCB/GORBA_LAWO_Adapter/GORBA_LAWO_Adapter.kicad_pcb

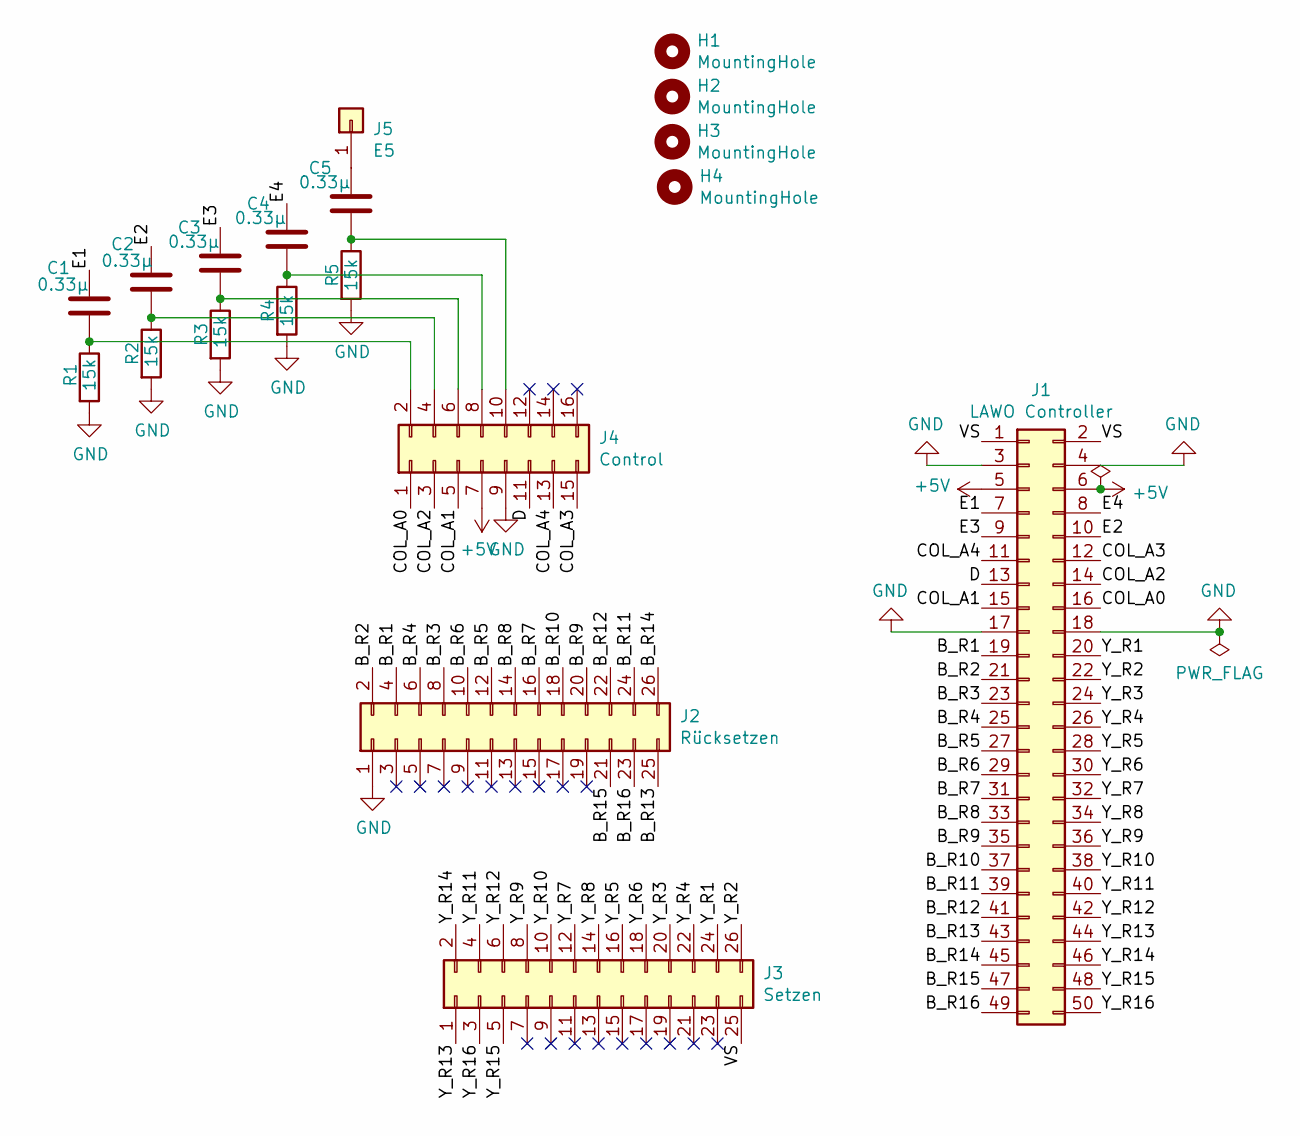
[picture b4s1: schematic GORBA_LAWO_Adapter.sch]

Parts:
C1, C2, C3, C4, C5: 0.33µ; C_Rect_L10.0mm_W4.0mm_P7.50mm_MKS4
H1, H2, H3, H4: MountingHole; MountingHole_2.7mm_Pad
J1: LAWO Controller; IDC_Header_Straight_50pins
J2: Rücksetzen; IDC_Header_Straight_26pins
J3: Setzen; IDC_Header_Straight_26pins
J4: Control; IDC_Header_Straight_16pins
J5: E5; PinHeader_1x01_P1.00mm_Vertical
R1, R2, R3, R4, R5: 15k; R_Axial_DIN0207_L6.3mm_D2.5mm_P7.62mm_Horizontal

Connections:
+5V: J1.5, J1.6, J4.7
/B_R1: J1.19, J2.4
/B_R2: J1.21, J2.2
/B_R3: J1.23, J2.8
/B_R4: J1.25, J2.6
/B_R5: J1.27, J2.12
/B_R6: J1.29, J2.10
/B_R7: J1.31, J2.16
/B_R8: J1.33, J2.14
/B_R9: J1.35, J2.20
/B_R10: J1.37, J2.18
/B_R11: J1.39, J2.24
/B_R12: J1.41, J2.22
/B_R13: J1.43, J2.25
/B_R14: J1.45, J2.26
/B_R15: J1.47, J2.21
/B_R16: J1.49, J2.23
/COL_A0: J1.16, J4.1
/COL_A1: J1.15, J4.5
/COL_A2: J1.14, J4.3
/COL_A3: J1.12, J4.15
/COL_A4: J1.11, J4.13
/D: J1.13, J4.11
/E1: C1.1, J1.7
/E2: C2.1, J1.10
/E3: C3.1, J1.9
/E4: C4.1, J1.8
/VS: J1.1, J1.2, J3.25
/Y_R1: J1.20, J3.24
/Y_R2: J1.22, J3.26
/Y_R3: J1.24, J3.20
/Y_R4: J1.26, J3.22
/Y_R5: J1.28, J3.16
/Y_R6: J1.30, J3.18
/Y_R7: J1.32, J3.12
/Y_R8: J1.34, J3.14
/Y_R9: J1.36, J3.8
/Y_R10: J1.38, J3.10
/Y_R11: J1.40, J3.4
/Y_R12: J1.42, J3.6
/Y_R13: J1.44, J3.1
/Y_R14: J1.46, J3.2
/Y_R15: J1.48, J3.5
/Y_R16: J1.50, J3.3
GND: J1.3, J1.4, J1.17, J1.18, J2.1, J4.9, R1.2, R2.2, R3.2, R4.2, R5.2
unnamed: C1.2, J4.2, R1.1
unnamed: C2.2, J4.4, R2.1
unnamed: C3.2, J4.6, R3.1
unnamed: C4.2, J4.8, R4.1
unnamed: C5.1, J5.1
unnamed: C5.2, J4.10, R5.1

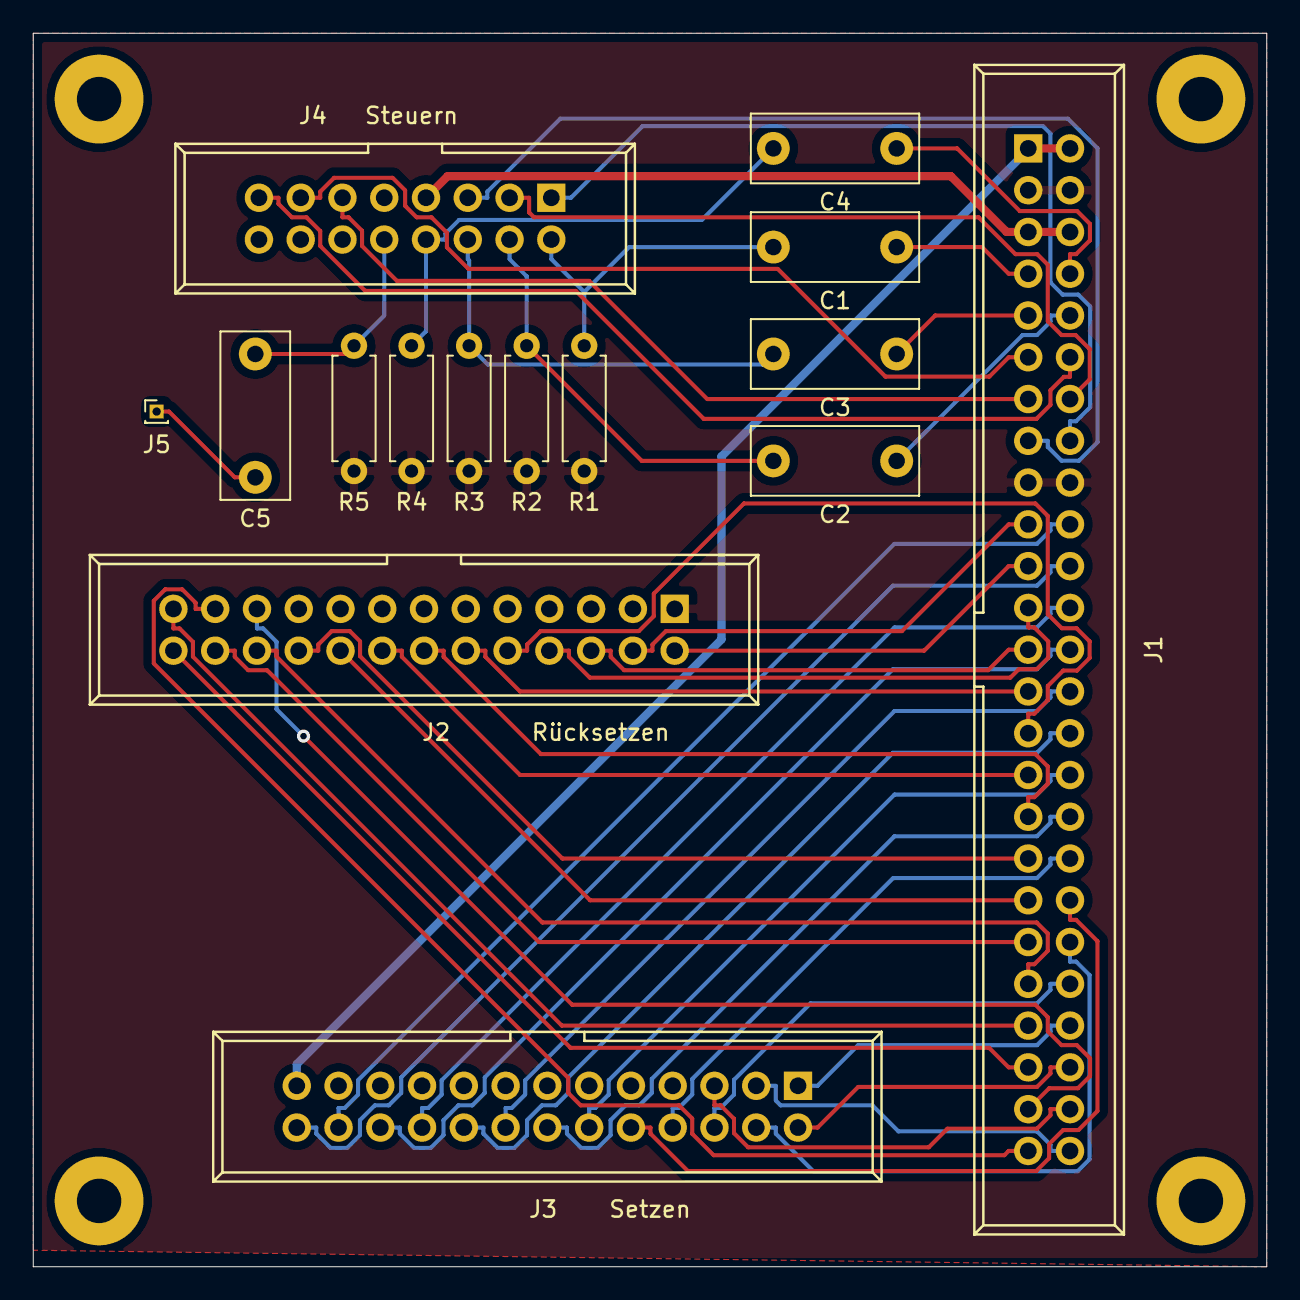
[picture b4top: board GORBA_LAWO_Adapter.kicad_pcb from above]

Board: 2 copper layers, 75.0 x 75.0 mm, 19 parts (0 on the bottom side), 51 nets.

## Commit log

2020-05-18 add images
2020-05-22 add library.properties
2020-05-24 improved 5x3 Font
2020-05-24 speed up I2C Writes
2020-05-29 add BROSE Panel
2020-05-29 add gitignore
2020-05-29 update BROSE_LAWO Adapter PCB
2020-05-29 add support for BROSE
2020-06-14 fix address
2020-06-15 add WEMOS_Adapter
2020-06-27 select Row before column
2020-06-27 add NUM_E_LINE_PINS to template
2020-07-04 update pcb
2020-07-04 fix brose panel
2020-07-04 fix repairpixel
2021-02-07 extend matrix width with virtual width to get "fade in" capabilities for long texts
